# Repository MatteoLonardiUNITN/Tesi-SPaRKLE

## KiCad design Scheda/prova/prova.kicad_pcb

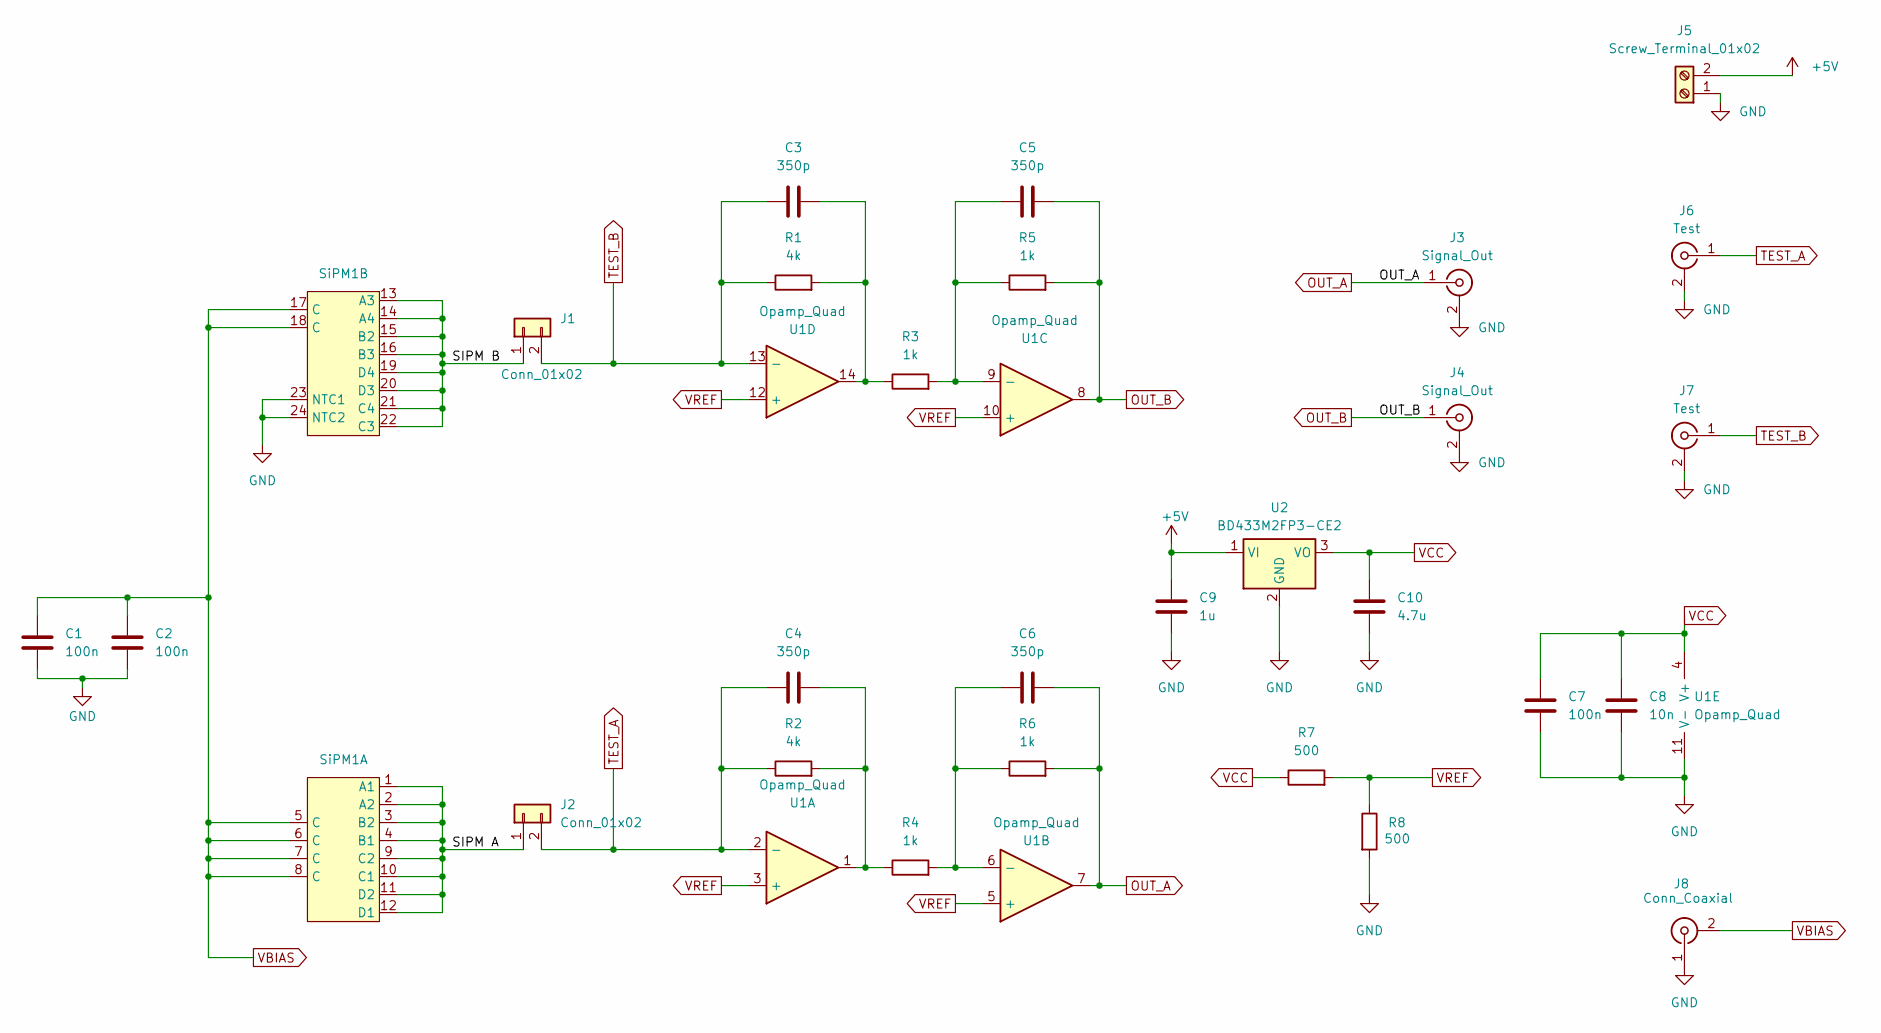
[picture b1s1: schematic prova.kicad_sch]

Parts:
C1, C2, C7: 100n; C_0603_1608Metric_Pad1.08x0.95mm_HandSolder
C3, C4, C5, C6: 350p; C_0603_1608Metric_Pad1.08x0.95mm_HandSolder
C8: 10n; C_0603_1608Metric_Pad1.08x0.95mm_HandSolder
C9: 1u; C_0603_1608Metric_Pad1.08x0.95mm_HandSolder
C10: 4.7u; C_0603_1608Metric_Pad1.08x0.95mm_HandSolder
J1, J2: Conn_01x02; PinHeader_1x02_P2.54mm_Vertical
J3, J4: Signal_Out; SMA_Horizontal
J5: Screw_Terminal_01x02; TerminalBlock_Altech_AK300-2_P5.00mm
J6, J7: Test; SMA_Horizontal
J8: Conn_Coaxial; BNC_Amphenol_B6252HB-NPP3G-50_Horizontal
R1, R2: 4k; R_0805_2012Metric_Pad1.20x1.40mm_HandSolder
R3, R4, R5, R6: 1k; R_0805_2012Metric_Pad1.20x1.40mm_HandSolder
R7, R8: 500; R_0805_2012Metric_Pad1.20x1.40mm_HandSolder
SiPM1: SiPM-Matrix
U1: Opamp_Quad; SOIC-14_3.9x8.7mm_P1.27mm
U2: BD433M2FP3-CE2; SOT-223-3_TabPin2

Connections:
+5V: C9.1, J5.2, U2.1 (VI)
/SIPM A: J2.1, SiPM1.1 (A1), SiPM1.2 (A2), SiPM1.3 (B2), SiPM1.4 (B1), SiPM1.9 (C2), SiPM1.10 (C1), SiPM1.11 (D2), SiPM1.12 (D1)
/SIPM B: J1.1, SiPM1.13 (A3), SiPM1.14 (A4), SiPM1.15 (B2), SiPM1.16 (B3), SiPM1.19 (D4), SiPM1.20 (D3), SiPM1.21 (C4), SiPM1.22 (C3)
GND: C1.2, C2.2, C7.2, C8.2, C9.2, C10.2, J3.2 (Ext), J4.2 (Ext), J5.1, J6.2 (Ext), J7.2 (Ext), J8.1 (In), R8.2, SiPM1.23 (NTC1), SiPM1.24 (NTC2), U1.11 (V-), U2.2 (GND)
unnamed: C3.2, R1.2, R3.1, U1.14
unnamed: C4.2, R2.2, R4.1, U1.1
unnamed: C6.1, R4.2, R6.1, U1.6 (-)
unnamed: C5.1, R3.2, R5.1, U1.9 (-)
OUT_A: C6.2, J3.1 (In), R6.2, U1.7
OUT_B: C5.2, J4.1 (In), R5.2, U1.8
TEST_A: C4.1, J2.2, J6.1 (In), R2.1, U1.2 (-)
TEST_B: C3.1, J1.2, J7.1 (In), R1.1, U1.13 (-)
VBIAS: C1.1, C2.1, J8.2 (Ext), SiPM1.5 (C), SiPM1.6 (C), SiPM1.7 (C), SiPM1.8 (C), SiPM1.17 (C), SiPM1.18 (C)
VCC: C7.1, C8.1, C10.1, R7.1, U1.4 (V+), U2.3 (VO)
VREF: R7.2, R8.1, U1.3 (+), U1.5 (+), U1.10 (+), U1.12 (+)

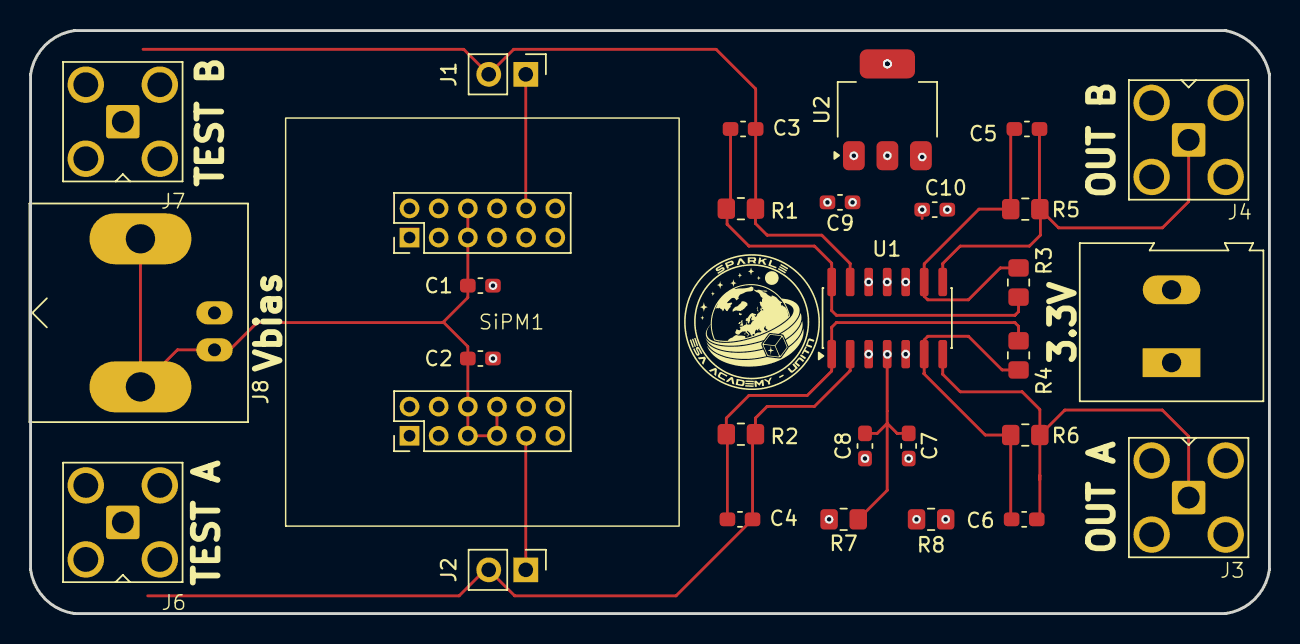
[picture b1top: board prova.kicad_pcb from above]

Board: 2 copper layers, 85.0 x 40.0 mm, 29 parts (0 on the bottom side), 15 nets.

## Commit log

2026-04-13 Primo Upload
    Primo upload dei tutti i file fin'ora per la tesi
2026-04-13 Convronto V I
    Confronto tra i segnali in uscita ai circuiti controllotensione e controllocorrente con analisi Trise e Tfall
2026-04-14 Aggiunta modelli 3D e regolatore
